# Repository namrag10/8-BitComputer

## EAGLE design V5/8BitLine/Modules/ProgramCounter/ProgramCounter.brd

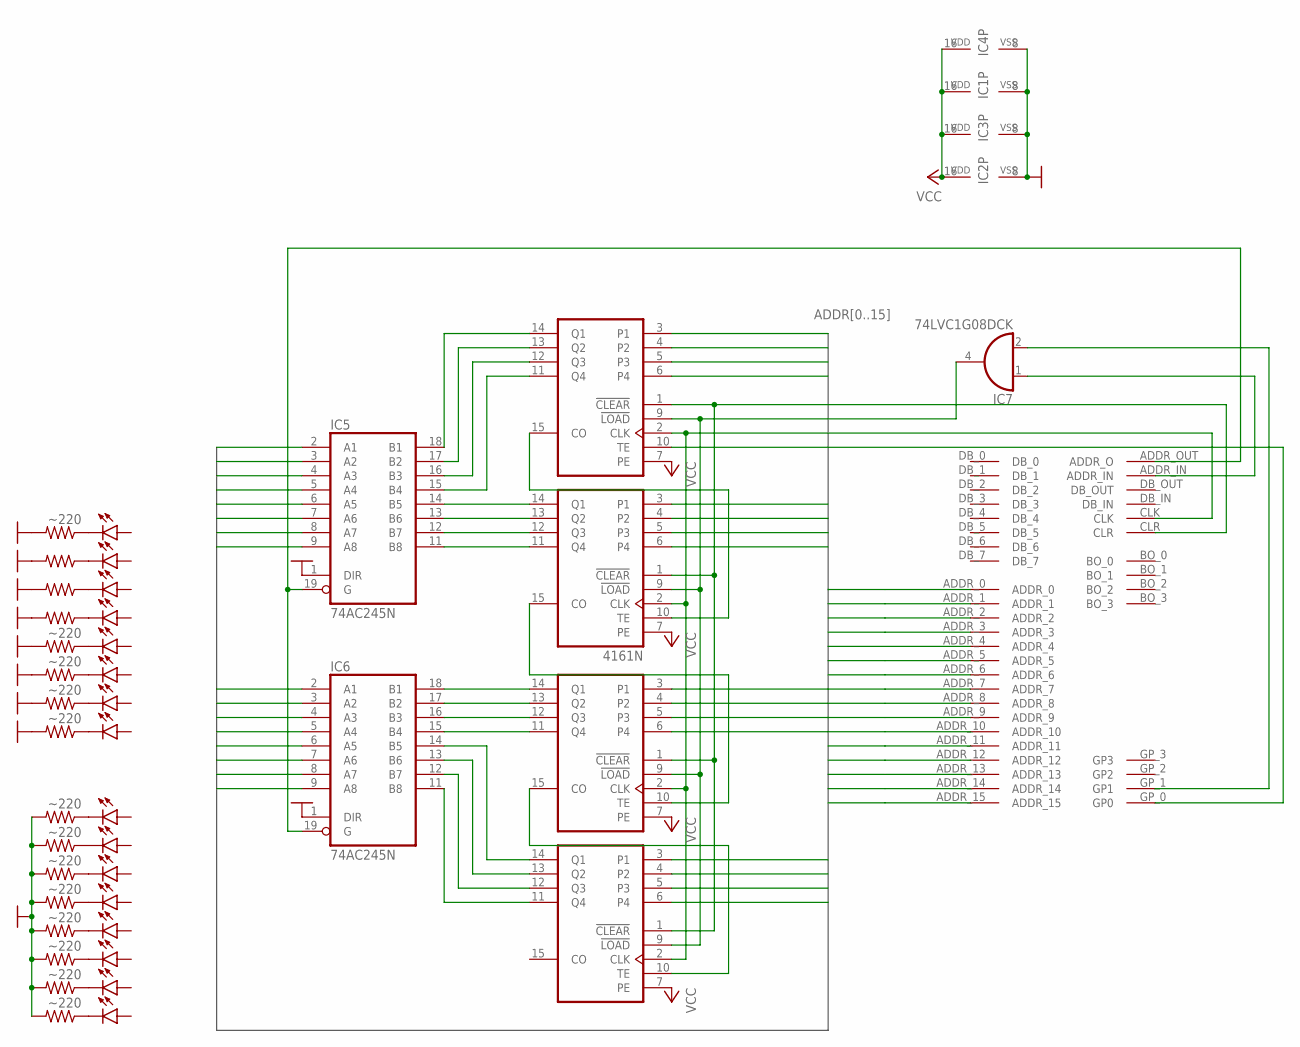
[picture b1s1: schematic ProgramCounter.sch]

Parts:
IC1, IC2, IC3, IC4: 4161N; DIL16
IC5, IC6: 74AC245N; DIL20
IC7: 74LVC1G08DCK; SC70-5
LED_A_REG_1, LED_A_REG_2, LED_A_REG_3, LED_A_REG_4, LED_A_REG_5, LED_A_REG_6, LED_A_REG_7, LED_A_REG_8, LED_A_REG_9, LED_A_REG_10, LED_A_REG_11, LED_A_REG_12, LED_A_REG_13, LED_A_REG_14, LED_A_REG_15, LED_A_REG_16: LED; LED5MM
R1, R2, R3, R4, R5, R6, R7, R8, R9, R10, R11, R12, R13, R14, R15, R16: ~220; 0204/7
U$1: BACKPLATE_INTERFACEEDGE_FINGER; BACK_INTERFACE-FOOT

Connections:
ADDR0: IC2.3 (P1), IC5.2 (A1), U$1.ADDR_0
ADDR1: IC2.4 (P2), IC5.3 (A2), U$1.ADDR_1
ADDR2: IC2.5 (P3), IC5.4 (A3), U$1.ADDR_2
ADDR3: IC2.6 (P4), IC5.5 (A4), U$1.ADDR_3
ADDR4: IC3.3 (P1), IC5.6 (A5), U$1.ADDR_4
ADDR5: IC3.4 (P2), IC5.7 (A6), U$1.ADDR_5
ADDR6: IC3.5 (P3), IC5.8 (A7), U$1.ADDR_6
ADDR7: IC3.6 (P4), IC5.9 (A8), U$1.ADDR_7
ADDR8: IC1.3 (P1), IC6.2 (A1), U$1.ADDR_8
ADDR9: IC1.4 (P2), IC6.3 (A2), U$1.ADDR_9
ADDR10: IC1.5 (P3), IC6.4 (A3), U$1.ADDR_10
ADDR11: IC1.6 (P4), IC6.5 (A4), U$1.ADDR_11
ADDR12: IC4.3 (P1), IC6.6 (A5), U$1.ADDR_12
ADDR13: IC4.4 (P2), IC6.7 (A6), U$1.ADDR_13
ADDR14: IC4.5 (P3), IC6.8 (A7), U$1.ADDR_14
ADDR15: IC4.6 (P4), IC6.9 (A8), U$1.ADDR_15
CONFIRMED_LOAD: IC1.9 (!LOAD), IC2.9 (!LOAD), IC3.9 (!LOAD), IC4.9 (!LOAD), IC7.4 (O)
GND: IC1.8 (VSS), IC2.8 (VSS), IC3.8 (VSS), IC4.8 (VSS), IC5.1 (DIR), IC5.10 (GND), IC6.1 (DIR), IC6.10 (GND), IC7.3 (GND), R1.2, R2.2, R3.2, R4.2, R5.2, R6.2, R7.2, R8.2, R9.2, R10.2, R11.2, R12.2, R13.2, R14.2, R15.2, R16.2, U$1.GND_0 (GND), U$1.GND_1 (GND)
LOAD_CONFIRMATION: IC7.2 (I1), U$1.GP_1 (GP1)
LOAD_REQUEST: IC7.1 (I0), U$1.ADDR_IN
unnamed: IC2.14 (Q1), IC5.18 (B1)
unnamed: IC2.13 (Q2), IC5.17 (B2)
unnamed: IC2.12 (Q3), IC5.16 (B3)
unnamed: IC2.11 (Q4), IC5.15 (B4)
unnamed: IC1.14 (Q1), IC6.18 (B1)
unnamed: IC3.13 (Q2), IC5.13 (B6)
unnamed: IC3.12 (Q3), IC5.12 (B7)
unnamed: IC3.11 (Q4), IC5.11 (B8)
unnamed: IC1.13 (Q2), IC6.17 (B2)
unnamed: IC1.12 (Q3), IC6.16 (B3)
unnamed: IC1.11 (Q4), IC6.15 (B4)
unnamed: IC4.11 (Q4), IC6.11 (B8)
unnamed: IC4.12 (Q3), IC6.12 (B7)
unnamed: IC4.13 (Q2), IC6.13 (B6)
unnamed: IC4.14 (Q1), IC6.14 (B5)
unnamed: IC1.2 (CLK), IC2.2 (CLK), IC3.2 (CLK), IC4.2 (CLK), U$1.CLK
unnamed: IC1.1 (!CLEAR), IC2.1 (!CLEAR), IC3.1 (!CLEAR), IC4.1 (!CLEAR), U$1.CLR
unnamed: IC2.15 (CO), IC3.10 (TE)
unnamed: IC1.10 (TE), IC3.15 (CO)
unnamed: IC1.15 (CO), IC4.10 (TE)
unnamed: IC2.10 (TE), U$1.GP_0 (GP0)
unnamed: IC5.19 (G), IC6.19 (G), U$1.ADDR_OUT (ADDR_O)
unnamed: LED_A_REG_1.K (C), R1.1
unnamed: LED_A_REG_10.K (C), R9.1
unnamed: LED_A_REG_11.K (C), R10.1
unnamed: LED_A_REG_12.K (C), R11.1
unnamed: LED_A_REG_13.K (C), R12.1
unnamed: LED_A_REG_14.K (C), R13.1
unnamed: LED_A_REG_15.K (C), R14.1
unnamed: LED_A_REG_16.K (C), R15.1
unnamed: LED_A_REG_9.K (C), R16.1
unnamed: IC3.14 (Q1), IC5.14 (B5)
unnamed: LED_A_REG_2.K (C), R2.1
unnamed: LED_A_REG_3.K (C), R3.1
unnamed: LED_A_REG_4.K (C), R4.1
unnamed: LED_A_REG_5.K (C), R5.1
unnamed: LED_A_REG_6.K (C), R6.1
unnamed: LED_A_REG_7.K (C), R7.1
unnamed: LED_A_REG_8.K (C), R8.1
VCC: IC1.7 (PE), IC1.16 (VDD), IC2.7 (PE), IC2.16 (VDD), IC3.7 (PE), IC3.16 (VDD), IC4.7 (PE), IC4.16 (VDD), IC5.20 (VCC), IC6.20 (VCC), IC7.5 (VCC), U$1.VCC_0 (VCC), U$1.VCC_1 (VCC)

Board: 2 copper layers, 40 parts (0 on the bottom side), 60 nets, no tracks yet.

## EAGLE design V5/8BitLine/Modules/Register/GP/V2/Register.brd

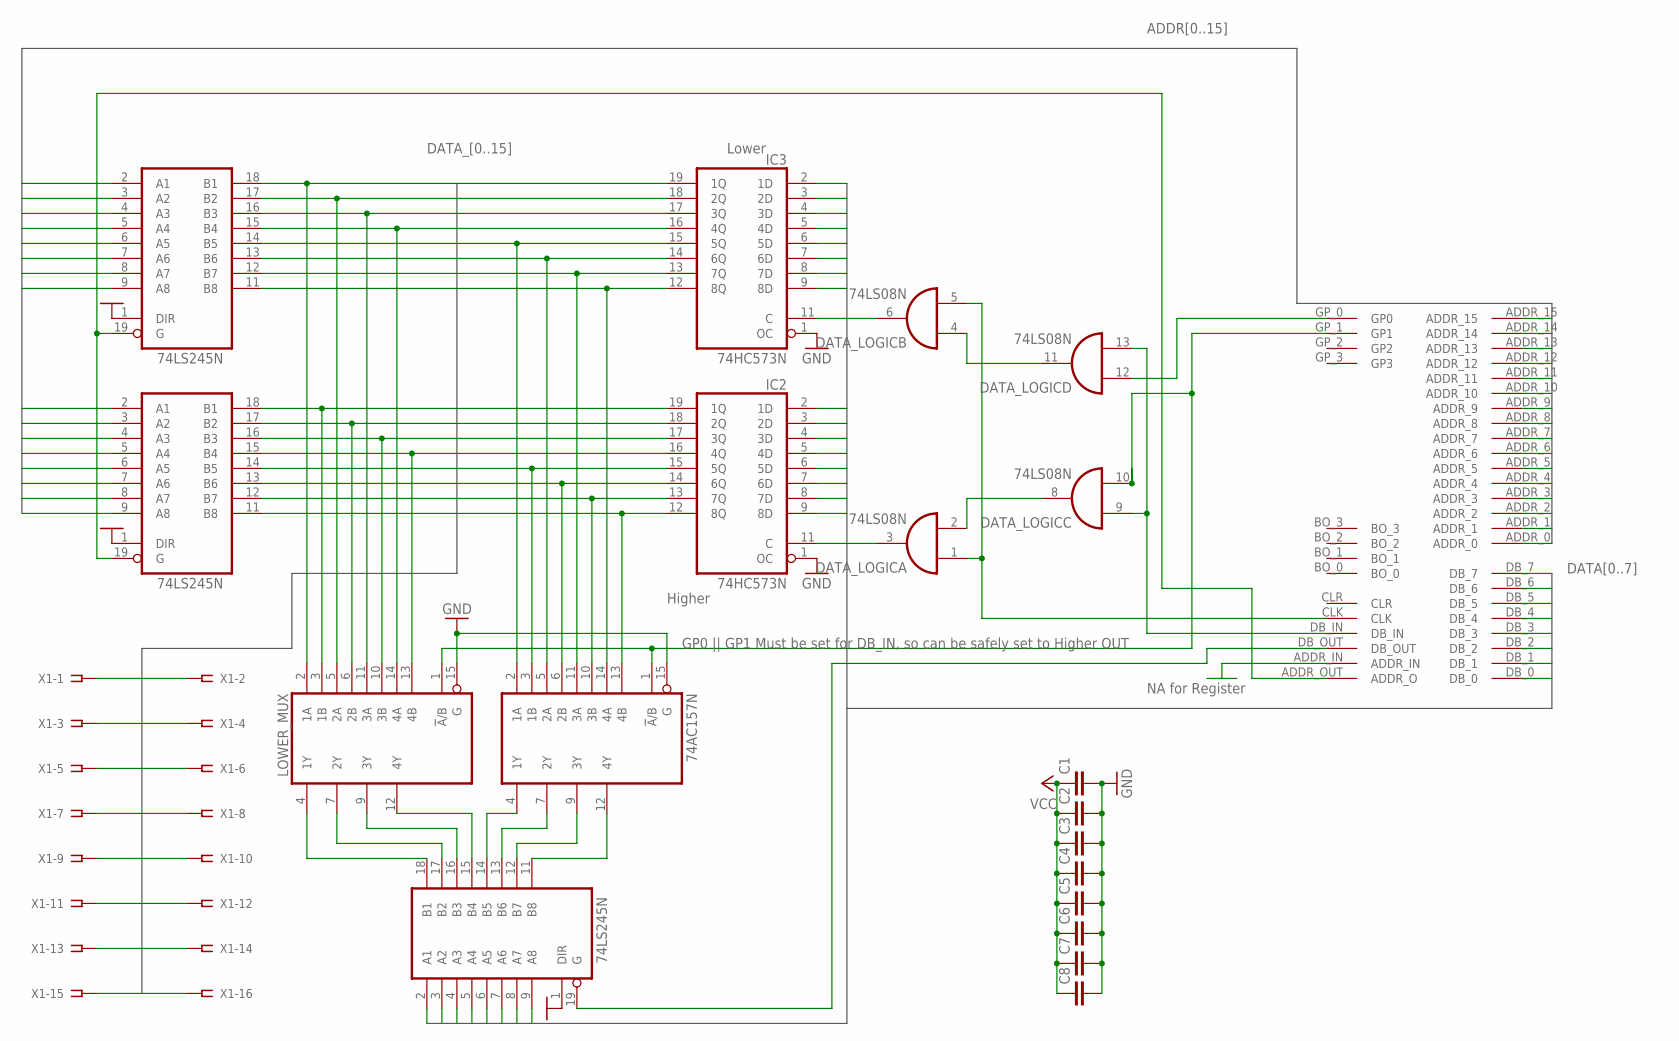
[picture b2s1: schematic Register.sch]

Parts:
ADDR_HIGHER_BUFFER: 74LS245N; DIL20
ADDR_LOWER_BUFFER: 74LS245N; DIL20
C1, C2, C3, C4, C5, C6, C7, C8: C2.5/2; C2.5-2
DATA_LOGIC: 74LS08N; DIL14
DATA_OUTPUT_BUFFER: 74LS245N; DIL20
HIGHER_MUX: 74AC157N; DIL16
IC2, IC3: 74HC573N; DIL20
LOWER_MUX: 74AC157N; DIL16
U$1: BACKPLATE_INTERFACEEDGE_FINGER; BACK_INTERFACE-FOOT
X1: SSW-108-02-G-D

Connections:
ADDR0: ADDR_LOWER_BUFFER.2 (A1), U$1.ADDR_0
ADDR1: ADDR_LOWER_BUFFER.3 (A2), U$1.ADDR_1
ADDR2: ADDR_LOWER_BUFFER.4 (A3), U$1.ADDR_2
ADDR3: ADDR_LOWER_BUFFER.5 (A4), U$1.ADDR_3
ADDR4: ADDR_LOWER_BUFFER.6 (A5), U$1.ADDR_4
ADDR5: ADDR_LOWER_BUFFER.7 (A6), U$1.ADDR_5
ADDR6: ADDR_LOWER_BUFFER.8 (A7), U$1.ADDR_6
ADDR7: ADDR_LOWER_BUFFER.9 (A8), U$1.ADDR_7
ADDR8: ADDR_HIGHER_BUFFER.2 (A1), U$1.ADDR_8
ADDR9: ADDR_HIGHER_BUFFER.3 (A2), U$1.ADDR_9
ADDR10: ADDR_HIGHER_BUFFER.4 (A3), U$1.ADDR_10
ADDR11: ADDR_HIGHER_BUFFER.5 (A4), U$1.ADDR_11
ADDR12: ADDR_HIGHER_BUFFER.6 (A5), U$1.ADDR_12
ADDR13: ADDR_HIGHER_BUFFER.7 (A6), U$1.ADDR_13
ADDR14: ADDR_HIGHER_BUFFER.8 (A7), U$1.ADDR_14
ADDR15: ADDR_HIGHER_BUFFER.9 (A8), U$1.ADDR_15
CLK: DATA_LOGIC.1 (I0), DATA_LOGIC.5 (I1), U$1.CLK
CTRL_ADDR_OUT: ADDR_HIGHER_BUFFER.19 (G), ADDR_LOWER_BUFFER.19 (G), U$1.ADDR_OUT (ADDR_O)
CTRL_DB_IN: DATA_LOGIC.9 (I0), DATA_LOGIC.13 (I1), U$1.DB_IN
CTRL_DB_OUT: DATA_OUTPUT_BUFFER.19 (G), U$1.DB_OUT
DATA0: DATA_OUTPUT_BUFFER.2 (A1), IC2.2 (1D), IC3.2 (1D), U$1.DB_0
DATA1: DATA_OUTPUT_BUFFER.3 (A2), IC2.3 (2D), IC3.3 (2D), U$1.DB_1
DATA2: DATA_OUTPUT_BUFFER.4 (A3), IC2.4 (3D), IC3.4 (3D), U$1.DB_2
DATA3: DATA_OUTPUT_BUFFER.5 (A4), IC2.5 (4D), IC3.5 (4D), U$1.DB_3
DATA4: DATA_OUTPUT_BUFFER.6 (A5), IC2.6 (5D), IC3.6 (5D), U$1.DB_4
DATA5: DATA_OUTPUT_BUFFER.7 (A6), IC2.7 (6D), IC3.7 (6D), U$1.DB_5
DATA6: DATA_OUTPUT_BUFFER.8 (A7), IC2.8 (7D), IC3.8 (7D), U$1.DB_6
DATA7: DATA_OUTPUT_BUFFER.9 (A8), IC2.9 (8D), IC3.9 (8D), U$1.DB_7
DATA_0: ADDR_LOWER_BUFFER.18 (B1), IC3.19 (1Q), LOWER_MUX.2 (1A), X1.15
DATA_1: ADDR_LOWER_BUFFER.17 (B2), IC3.18 (2Q), LOWER_MUX.5 (2A), X1.13
DATA_2: ADDR_LOWER_BUFFER.16 (B3), IC3.17 (3Q), LOWER_MUX.11 (3A), X1.11
DATA_3: ADDR_LOWER_BUFFER.15 (B4), IC3.16 (4Q), LOWER_MUX.14 (4A), X1.9
DATA_4: ADDR_LOWER_BUFFER.14 (B5), HIGHER_MUX.2 (1A), IC3.15 (5Q), X1.7
DATA_5: ADDR_LOWER_BUFFER.13 (B6), HIGHER_MUX.5 (2A), IC3.14 (6Q), X1.5
DATA_6: ADDR_LOWER_BUFFER.12 (B7), HIGHER_MUX.11 (3A), IC3.13 (7Q), X1.3
DATA_7: ADDR_LOWER_BUFFER.11 (B8), HIGHER_MUX.14 (4A), IC3.12 (8Q), X1.1
DATA_8: ADDR_HIGHER_BUFFER.18 (B1), IC2.19 (1Q), LOWER_MUX.3 (1B), X1.2
DATA_9: ADDR_HIGHER_BUFFER.17 (B2), IC2.18 (2Q), LOWER_MUX.6 (2B), X1.4
DATA_10: ADDR_HIGHER_BUFFER.16 (B3), IC2.17 (3Q), LOWER_MUX.10 (3B), X1.6
DATA_11: ADDR_HIGHER_BUFFER.15 (B4), IC2.16 (4Q), LOWER_MUX.13 (4B), X1.8
DATA_12: ADDR_HIGHER_BUFFER.14 (B5), HIGHER_MUX.3 (1B), IC2.15 (5Q), X1.10
DATA_13: ADDR_HIGHER_BUFFER.13 (B6), HIGHER_MUX.6 (2B), IC2.14 (6Q), X1.12
DATA_14: ADDR_HIGHER_BUFFER.12 (B7), HIGHER_MUX.10 (3B), IC2.13 (7Q), X1.14
DATA_15: ADDR_HIGHER_BUFFER.11 (B8), HIGHER_MUX.13 (4B), IC2.12 (8Q), X1.16
GND: ADDR_HIGHER_BUFFER.1 (DIR), ADDR_HIGHER_BUFFER.10 (GND), ADDR_LOWER_BUFFER.1 (DIR), ADDR_LOWER_BUFFER.10 (GND), C1.2, C2.2, C3.2, C4.2, C5.2, C6.2, C7.2, C8.2, DATA_LOGIC.7 (GND), DATA_OUTPUT_BUFFER.1 (DIR), DATA_OUTPUT_BUFFER.10 (GND), HIGHER_MUX.8 (GND), HIGHER_MUX.15 (G), IC2.1 (OC), IC2.10 (GND), IC3.1 (OC), IC3.10 (GND), LOWER_MUX.8 (GND), LOWER_MUX.15 (G), U$1.GND_0 (GND), U$1.GND_1 (GND)
GP_0: DATA_LOGIC.12 (I0), U$1.GP_0 (GP0)
GP_1: DATA_LOGIC.10 (I1), HIGHER_MUX.1 (!A!/B), LOWER_MUX.1 (!A!/B), U$1.GP_1 (GP1)
unnamed: DATA_OUTPUT_BUFFER.18 (B1), LOWER_MUX.4 (1Y)
unnamed: DATA_OUTPUT_BUFFER.17 (B2), LOWER_MUX.7 (2Y)
unnamed: DATA_LOGIC.6 (O), IC3.11 (C)
unnamed: DATA_LOGIC.3 (O), IC2.11 (C)
unnamed: DATA_LOGIC.4 (I0), DATA_LOGIC.11 (O)
unnamed: DATA_LOGIC.2 (I1), DATA_LOGIC.8 (O)
unnamed: DATA_OUTPUT_BUFFER.16 (B3), LOWER_MUX.9 (3Y)
unnamed: DATA_OUTPUT_BUFFER.15 (B4), LOWER_MUX.12 (4Y)
unnamed: DATA_OUTPUT_BUFFER.14 (B5), HIGHER_MUX.4 (1Y)
unnamed: DATA_OUTPUT_BUFFER.13 (B6), HIGHER_MUX.7 (2Y)
unnamed: DATA_OUTPUT_BUFFER.12 (B7), HIGHER_MUX.9 (3Y)
unnamed: DATA_OUTPUT_BUFFER.11 (B8), HIGHER_MUX.12 (4Y)
VCC: ADDR_HIGHER_BUFFER.20 (VCC), ADDR_LOWER_BUFFER.20 (VCC), C1.1, C2.1, C3.1, C4.1, C5.1, C6.1, C7.1, C8.1, DATA_LOGIC.14 (VCC), DATA_OUTPUT_BUFFER.20 (VCC), HIGHER_MUX.16 (VCC), IC2.20 (VCC), IC3.20 (VCC), LOWER_MUX.16 (VCC), U$1.VCC_0 (VCC), U$1.VCC_1 (VCC)

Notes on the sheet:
Lower
Higher
GP0 || GP1 Must be set for DB_IN, so can be safely set to Higher OUT
NA for Register

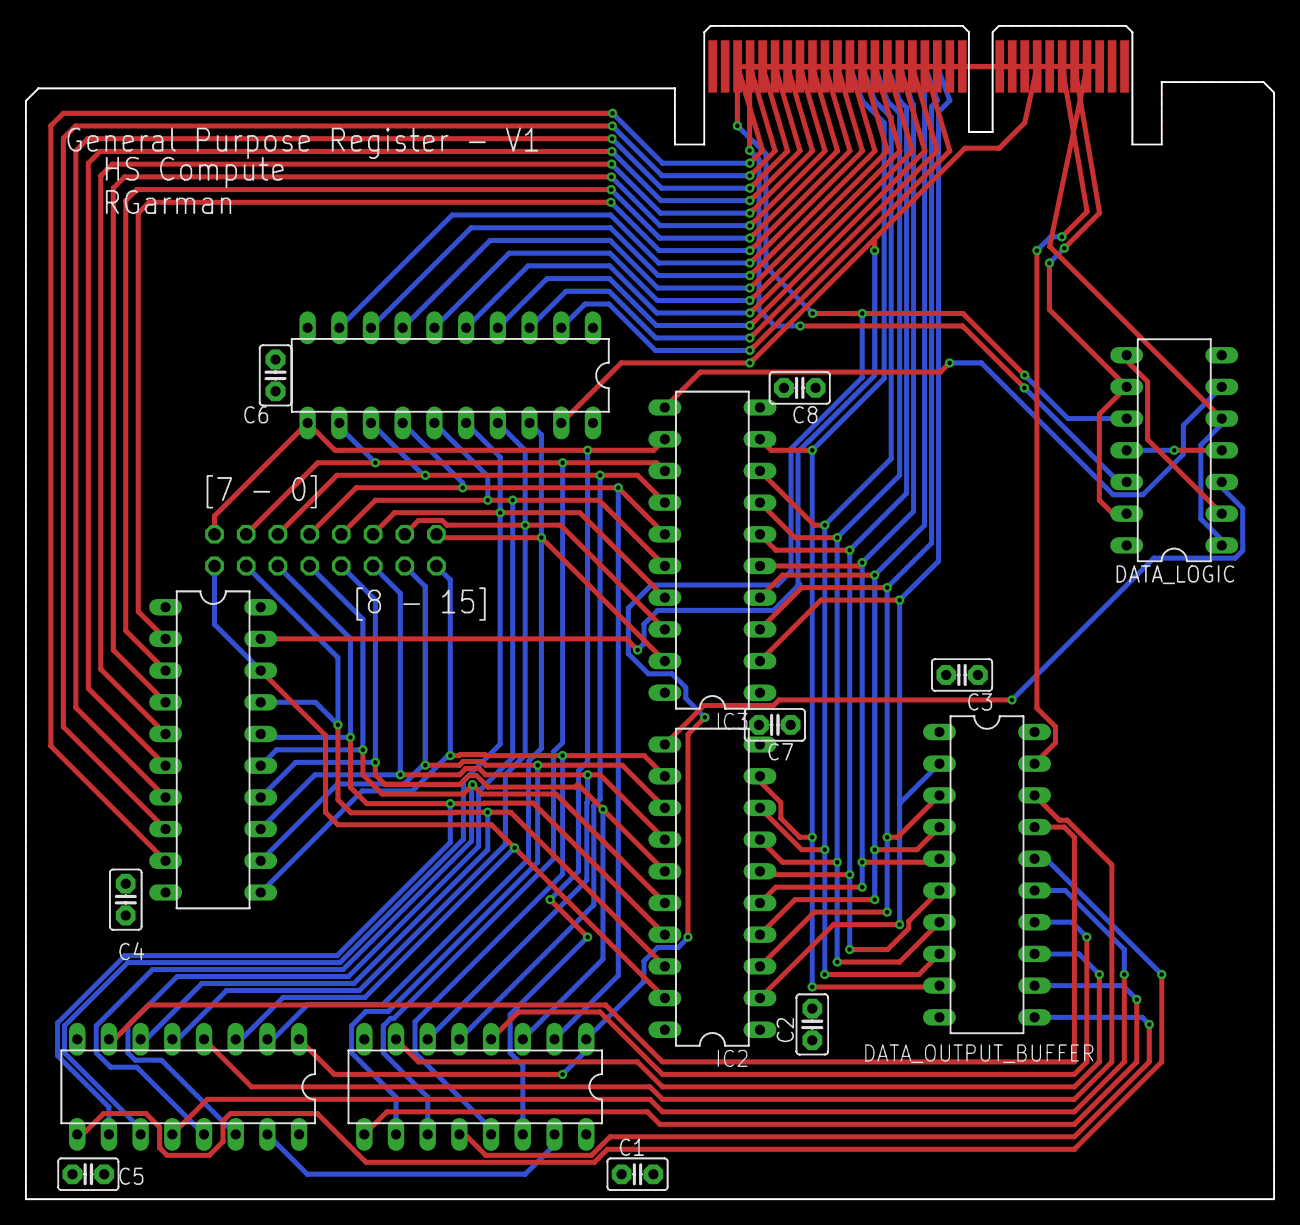
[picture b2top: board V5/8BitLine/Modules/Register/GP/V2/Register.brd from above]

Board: 2 copper layers, 100.0 x 94.0 mm, 18 parts (1 on the bottom side), 60 nets.

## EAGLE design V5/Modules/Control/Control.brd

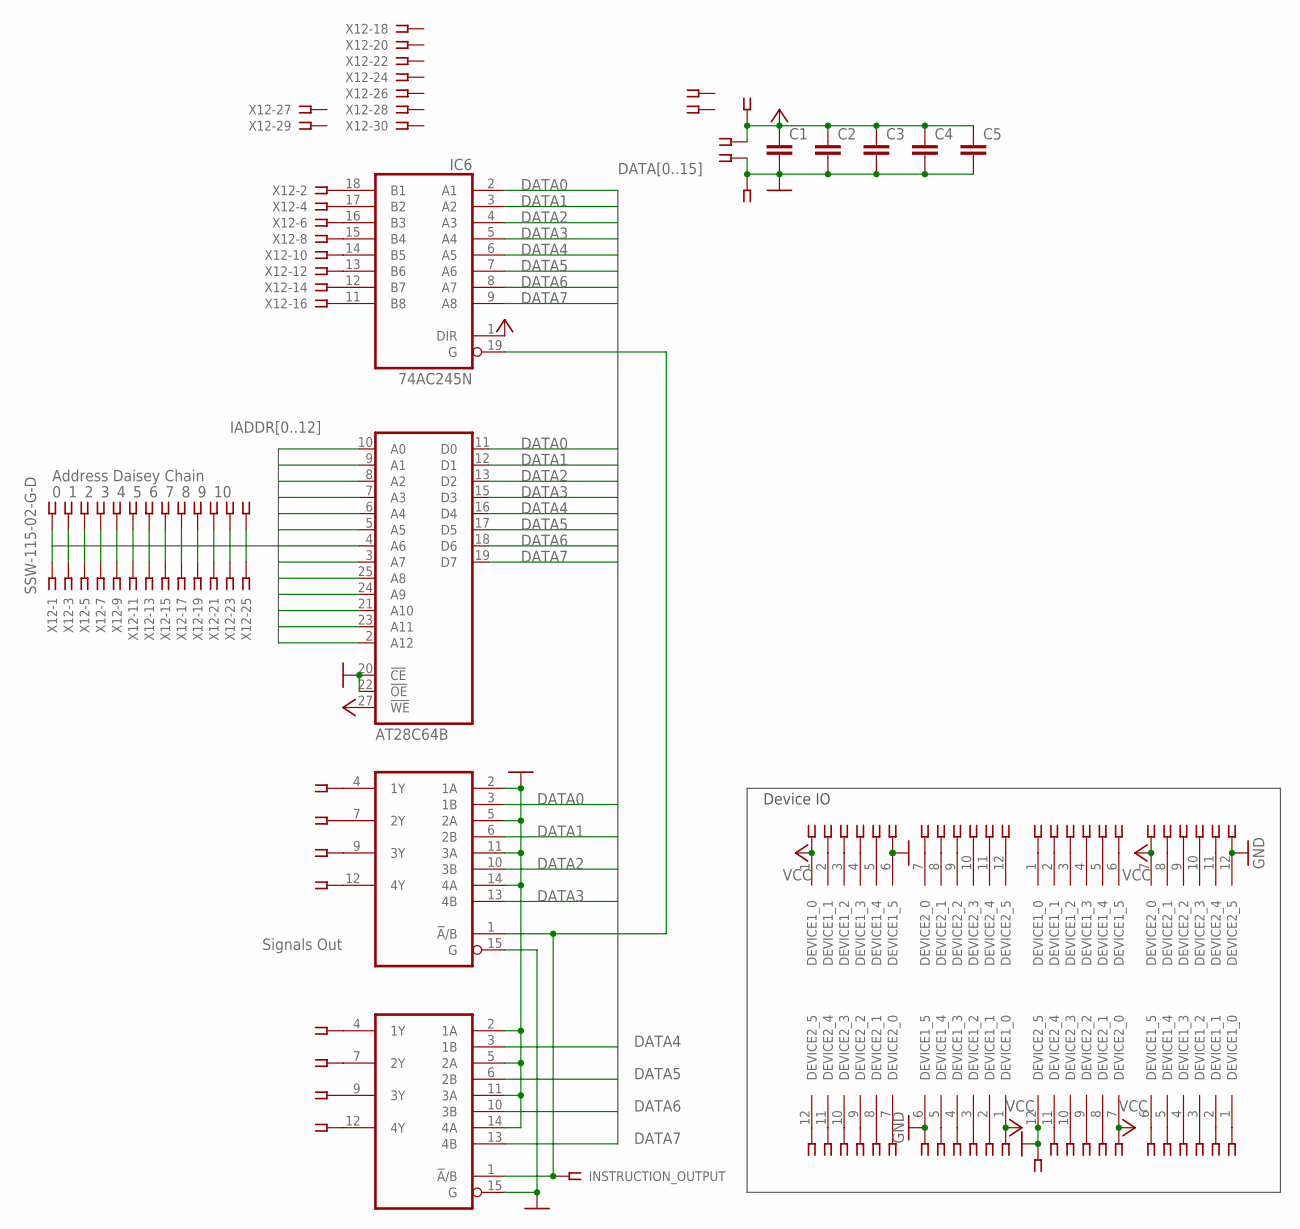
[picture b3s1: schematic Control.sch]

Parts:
C1, C2, C3, C4, C5: C2.5/2; C2.5-2
IC4, IC5: 74AC157N; DIL16
IC6: 74AC245N; DIL20
INSTRUCTION_OUTPUT: SSW-101-02-G-S
U$1, U$2, U$4, U$5: CONTROL_SIG-INT; CONTROL_SIG-INT-FOOT
U$3: AT28C64B; DIP28-WIDE
X1, X2, X3, X4, X6, X7, X8, X9: SSW-106-02-G-S
X5: SSW-108-02-G-S
X10: SSW-113-02-G-S
X11: SSW-102-02-G-S
X12: SSW-115-02-G-D
X13: SSW-104-02-G-S

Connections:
DATA0: IC4.3 (1B), IC6.2 (A1), U$3.11 (D0)
DATA1: IC4.6 (2B), IC6.3 (A2), U$3.12 (D1)
DATA2: IC4.10 (3B), IC6.4 (A3), U$3.13 (D2)
DATA3: IC4.13 (4B), IC6.5 (A4), U$3.15 (D3)
DATA4: IC5.3 (1B), IC6.6 (A5), U$3.16 (D4)
DATA5: IC5.6 (2B), IC6.7 (A6), U$3.17 (D5)
DATA6: IC5.10 (3B), IC6.8 (A7), U$3.18 (D6)
DATA7: IC5.13 (4B), IC6.9 (A8), U$3.19 (D7)
GND: C1.2, C2.2, C3.2, C4.2, C5.2, IC4.2 (1A), IC4.5 (2A), IC4.8 (GND), IC4.11 (3A), IC4.14 (4A), IC4.15 (G), IC5.2 (1A), IC5.5 (2A), IC5.8 (GND), IC5.11 (3A), IC5.14 (4A), IC5.15 (G), IC6.10 (GND), U$1.6 (DEVICE1_5), U$2.12 (DEVICE2_5), U$3.14 (GND), U$3.20 (!CE), U$3.22 (!OE), U$4.12 (DEVICE2_5), U$5.6 (DEVICE1_5), X1.1, X4.1, X7.1, X8.1, X11.2, X13.4
IADDR0: U$3.10 (A0), X10.13, X12.1
IADDR1: U$3.9 (A1), X10.12, X12.3
IADDR2: U$3.8 (A2), X10.11, X12.5
IADDR3: U$3.7 (A3), X10.10, X12.7
IADDR4: U$3.6 (A4), X10.9, X12.9
IADDR5: U$3.5 (A5), X10.8, X12.11
IADDR6: U$3.4 (A6), X10.7, X12.13
IADDR7: U$3.3 (A7), X10.6, X12.15
IADDR8: U$3.25 (A8), X10.5, X12.17
IADDR9: U$3.24 (A9), X10.4, X12.19
IADDR10: U$3.21 (A10), X10.3, X12.21
IADDR11: U$3.23 (A11), X10.2, X12.23
IADDR12: U$3.2 (A12), X10.1, X12.25
unnamed: U$2.6 (DEVICE1_5), X6.1
unnamed: U$2.5 (DEVICE1_4), X6.2
unnamed: U$2.4 (DEVICE1_3), X6.3
unnamed: U$2.3 (DEVICE1_2), X6.4
unnamed: U$2.2 (DEVICE1_1), X6.5
unnamed: U$2.1 (DEVICE1_0), X6.6
unnamed: U$2.11 (DEVICE2_4), X7.2
unnamed: U$2.10 (DEVICE2_3), X7.3
unnamed: U$2.9 (DEVICE2_2), X7.4
unnamed: U$2.8 (DEVICE2_1), X7.5
unnamed: U$4.6 (DEVICE1_5), X3.1
unnamed: U$4.5 (DEVICE1_4), X3.2
unnamed: U$4.4 (DEVICE1_3), X3.3
unnamed: U$4.3 (DEVICE1_2), X3.4
unnamed: U$4.2 (DEVICE1_1), X3.5
unnamed: U$4.1 (DEVICE1_0), X3.6
unnamed: U$4.11 (DEVICE2_4), X4.2
unnamed: U$4.10 (DEVICE2_3), X4.3
unnamed: U$4.9 (DEVICE2_2), X4.4
unnamed: U$4.8 (DEVICE2_1), X4.5
unnamed: U$5.5 (DEVICE1_4), X1.2
unnamed: U$5.4 (DEVICE1_3), X1.3
unnamed: U$5.3 (DEVICE1_2), X1.4
unnamed: U$5.2 (DEVICE1_1), X1.5
unnamed: U$5.12 (DEVICE2_5), X2.1
unnamed: U$5.11 (DEVICE2_4), X2.2
unnamed: U$5.10 (DEVICE2_3), X2.3
unnamed: U$5.9 (DEVICE2_2), X2.4
unnamed: U$5.8 (DEVICE2_1), X2.5
unnamed: U$5.7 (DEVICE2_0), X2.6
unnamed: U$1.5 (DEVICE1_4), X8.2
unnamed: U$1.4 (DEVICE1_3), X8.3
unnamed: U$1.3 (DEVICE1_2), X8.4
unnamed: U$1.2 (DEVICE1_1), X8.5
unnamed: U$1.12 (DEVICE2_5), X9.1
unnamed: U$1.11 (DEVICE2_4), X9.2
unnamed: U$1.10 (DEVICE2_3), X9.3
unnamed: U$1.9 (DEVICE2_2), X9.4
unnamed: U$1.8 (DEVICE2_1), X9.5
unnamed: U$1.7 (DEVICE2_0), X9.6
unnamed: IC6.18 (B1), X12.2
unnamed: IC6.17 (B2), X12.4
unnamed: IC6.16 (B3), X12.6
unnamed: IC6.15 (B4), X12.8
unnamed: IC6.14 (B5), X12.10
unnamed: IC6.13 (B6), X12.12
unnamed: IC6.12 (B7), X12.14
unnamed: IC6.11 (B8), X12.16
unnamed: IC5.12 (4Y), X5.1
unnamed: IC5.9 (3Y), X5.2
unnamed: IC4.1 (!A!/B), IC5.1 (!A!/B), IC6.19 (G), INSTRUCTION_OUTPUT.1
unnamed: IC5.7 (2Y), X5.3
unnamed: IC5.4 (1Y), X5.4
unnamed: IC4.12 (4Y), X5.5
unnamed: IC4.9 (3Y), X5.6
unnamed: IC4.7 (2Y), X5.7
unnamed: IC4.4 (1Y), X5.8
VCC: C1.1, C2.1, C3.1, C4.1, C5.1, IC4.16 (VCC), IC5.16 (VCC), IC6.1 (DIR), IC6.20 (VCC), U$1.1 (DEVICE1_0), U$2.7 (DEVICE2_0), U$3.27 (!WE), U$3.28 (VCC), U$4.7 (DEVICE2_0), U$5.1 (DEVICE1_0), X1.6, X4.6, X7.6, X8.6, X11.1, X13.1

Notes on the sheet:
Device IO
Address Daisey Chain
Signals Out

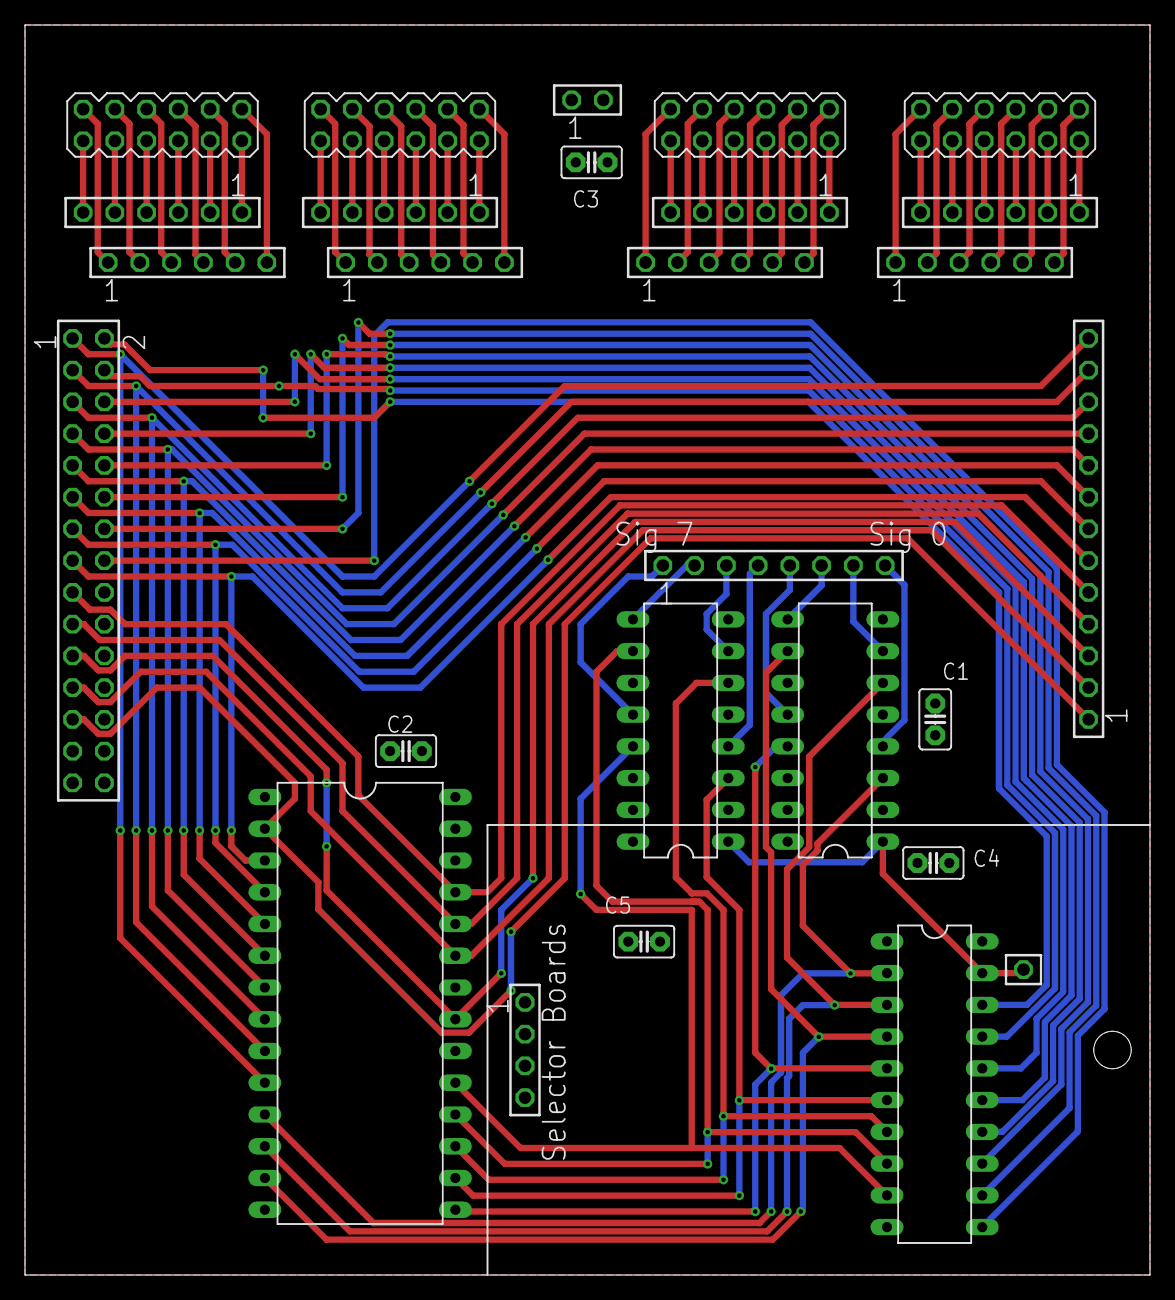
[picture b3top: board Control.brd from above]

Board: 2 copper layers, 90.0 x 100.0 mm, 27 parts (0 on the bottom side), 80 nets.

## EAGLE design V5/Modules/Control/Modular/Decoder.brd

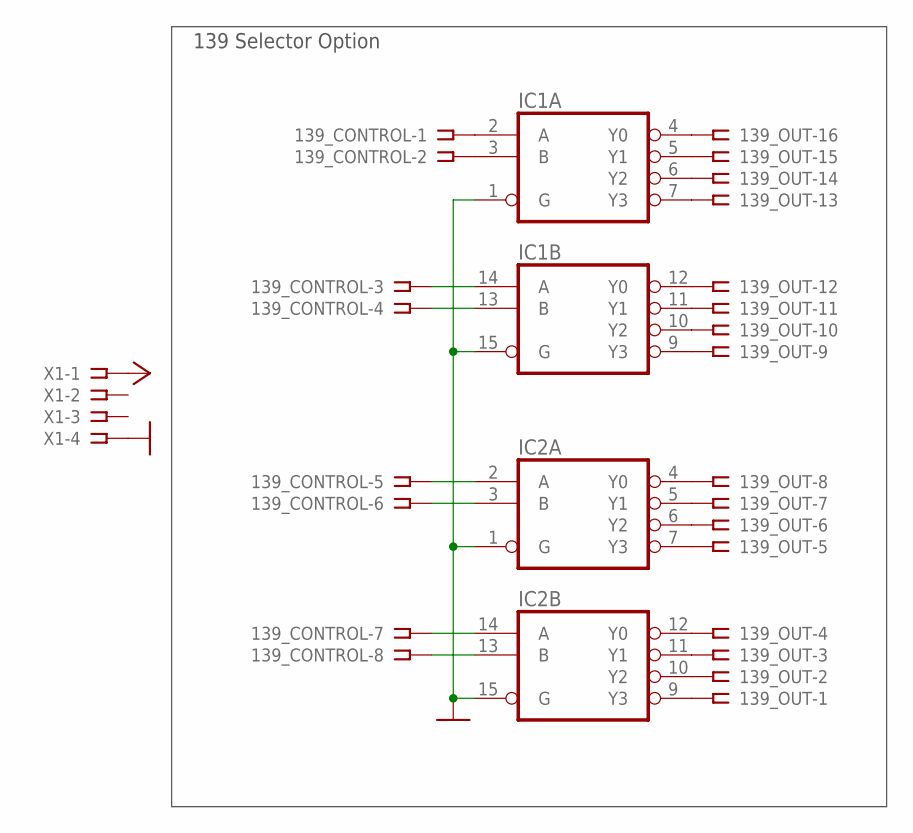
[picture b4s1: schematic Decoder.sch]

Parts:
139_CONTROL: SSW-108-02-G-S
139_OUT: SSW-116-02-G-S
IC1, IC2: 74AC139N; DIL16
X1: SSW-104-02-G-S

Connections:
GND: IC1.1 (G), IC1.8 (GND), IC1.15 (G), IC2.1 (G), IC2.8 (GND), IC2.15 (G), X1.4
unnamed: 139_OUT.13, IC1.7 (Y3)
unnamed: 139_OUT.14, IC1.6 (Y2)
unnamed: 139_OUT.15, IC1.5 (Y1)
unnamed: 139_OUT.16, IC1.4 (Y0)
unnamed: 139_OUT.9, IC1.9 (Y3)
unnamed: 139_OUT.10, IC1.10 (Y2)
unnamed: 139_OUT.11, IC1.11 (Y1)
unnamed: 139_OUT.12, IC1.12 (Y0)
unnamed: 139_OUT.5, IC2.7 (Y3)
unnamed: 139_OUT.6, IC2.6 (Y2)
unnamed: 139_OUT.7, IC2.5 (Y1)
unnamed: 139_OUT.8, IC2.4 (Y0)
unnamed: 139_OUT.1, IC2.9 (Y3)
unnamed: 139_OUT.2, IC2.10 (Y2)
unnamed: 139_OUT.3, IC2.11 (Y1)
unnamed: 139_OUT.4, IC2.12 (Y0)
unnamed: 139_CONTROL.1, IC1.2 (A)
unnamed: 139_CONTROL.2, IC1.3 (B)
unnamed: 139_CONTROL.8, IC2.13 (B)
unnamed: 139_CONTROL.7, IC2.14 (A)
unnamed: 139_CONTROL.6, IC2.3 (B)
unnamed: 139_CONTROL.5, IC2.2 (A)
unnamed: 139_CONTROL.4, IC1.13 (B)
unnamed: 139_CONTROL.3, IC1.14 (A)
VCC: IC1.16 (VCC), IC2.16 (VCC), X1.1

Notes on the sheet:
139 Selector Option

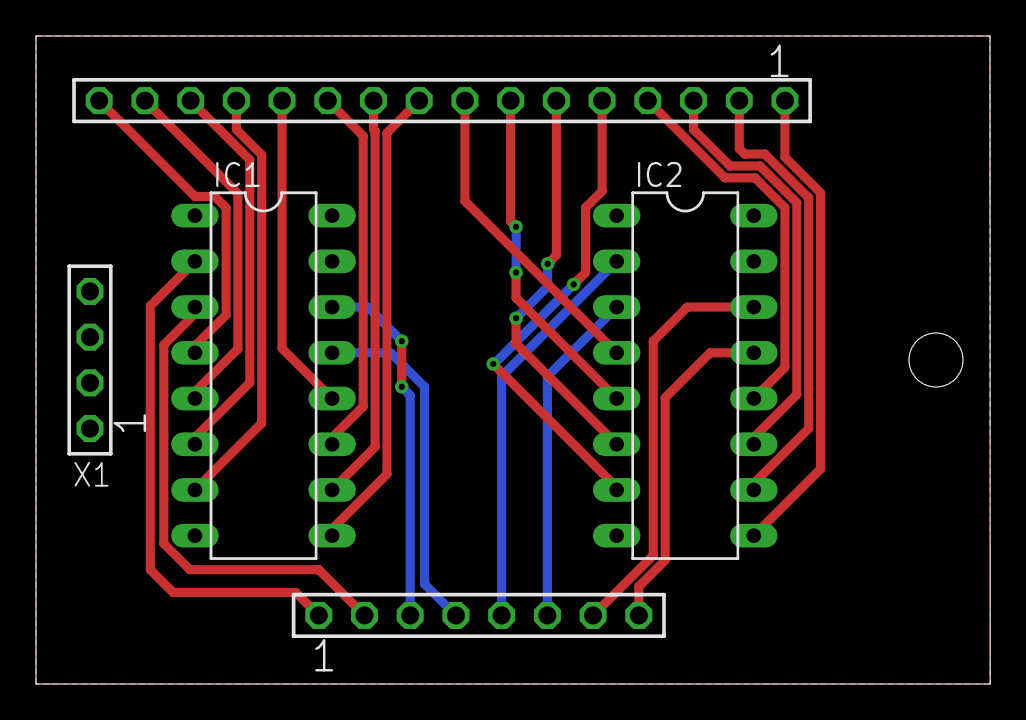
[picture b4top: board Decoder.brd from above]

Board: 2 copper layers, 53.0 x 36.0 mm, 5 parts (0 on the bottom side), 26 nets.

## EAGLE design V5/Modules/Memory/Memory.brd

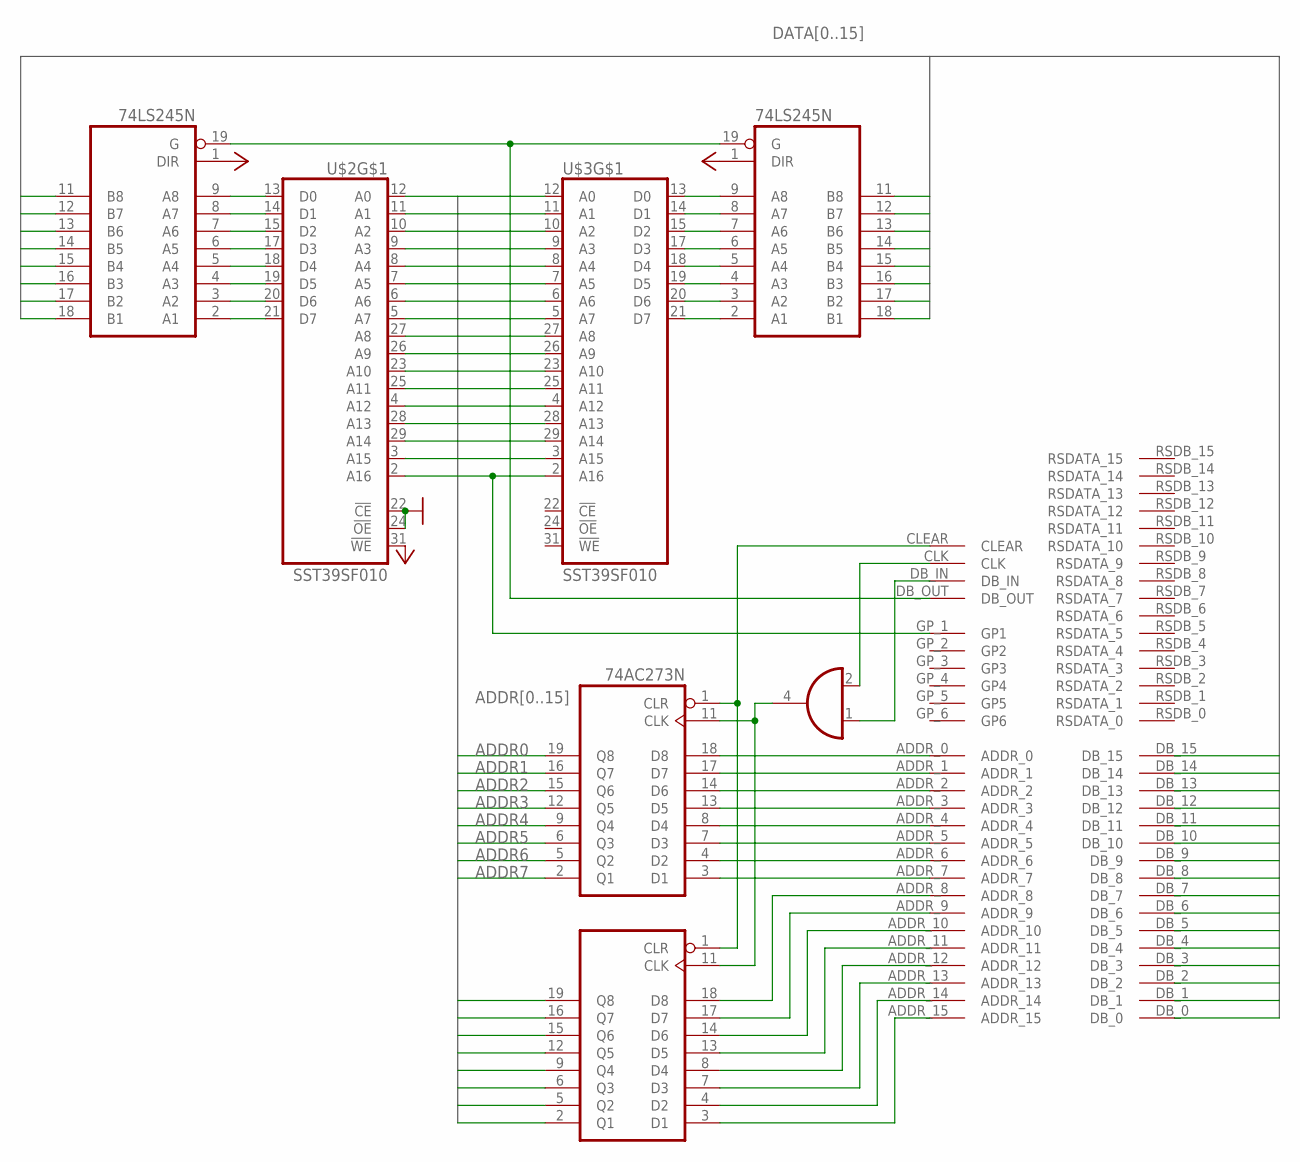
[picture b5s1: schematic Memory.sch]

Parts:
IC1, IC2: 74AC273N; DIL20
IC4: 74AHC1G08DCK; SC70-5
OUTPUT_BUFFER_MEMORY, OUTPUT_BUFFER_MEMORY1: 74LS245N; DIL20
U$1: BACKPLATE_INTERFACE; BACK_INTERFACE-FOOT
U$2, U$3: SST39SF010; DIP32-WIDE

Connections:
ADDR0: IC1.19 (Q8), U$2.12 (A0), U$3.12 (A0)
ADDR1: IC1.16 (Q7), U$2.11 (A1), U$3.11 (A1)
ADDR2: IC1.15 (Q6), U$2.10 (A2), U$3.10 (A2)
ADDR3: IC1.12 (Q5), U$2.9 (A3), U$3.9 (A3)
ADDR4: IC1.9 (Q4), U$2.8 (A4), U$3.8 (A4)
ADDR5: IC1.6 (Q3), U$2.7 (A5), U$3.7 (A5)
ADDR6: IC1.5 (Q2), U$2.6 (A6), U$3.6 (A6)
ADDR7: IC1.2 (Q1), U$2.5 (A7), U$3.5 (A7)
ADDR8: IC2.19 (Q8), U$2.27 (A8), U$3.27 (A8)
ADDR9: IC2.16 (Q7), U$2.26 (A9), U$3.26 (A9)
ADDR10: IC2.15 (Q6), U$2.23 (A10), U$3.23 (A10)
ADDR11: IC2.12 (Q5), U$2.25 (A11), U$3.25 (A11)
ADDR12: IC2.9 (Q4), U$2.4 (A12), U$3.4 (A12)
ADDR13: IC2.6 (Q3), U$2.28 (A13), U$3.28 (A13)
ADDR14: IC2.5 (Q2), U$2.3 (A15), U$2.29 (A14), U$3.29 (A14)
ADDR15: IC2.2 (Q1), U$3.3 (A15)
DATA0: OUTPUT_BUFFER_MEMORY.11 (B8), U$1.DB_0
DATA1: OUTPUT_BUFFER_MEMORY.12 (B7), U$1.DB_1
DATA2: OUTPUT_BUFFER_MEMORY.13 (B6), U$1.DB_2
DATA3: OUTPUT_BUFFER_MEMORY.14 (B5), U$1.DB_3
DATA4: OUTPUT_BUFFER_MEMORY.15 (B4), U$1.DB_4
DATA5: OUTPUT_BUFFER_MEMORY.16 (B3), U$1.DB_5
DATA6: OUTPUT_BUFFER_MEMORY.17 (B2), U$1.DB_6
DATA7: OUTPUT_BUFFER_MEMORY.18 (B1), U$1.DB_7
DATA8: OUTPUT_BUFFER_MEMORY1.11 (B8), U$1.DB_8
DATA9: OUTPUT_BUFFER_MEMORY1.12 (B7), U$1.DB_9
DATA10: OUTPUT_BUFFER_MEMORY1.13 (B6), U$1.DB_10
DATA11: OUTPUT_BUFFER_MEMORY1.14 (B5), U$1.DB_11
DATA12: OUTPUT_BUFFER_MEMORY1.15 (B4), U$1.DB_12
DATA13: OUTPUT_BUFFER_MEMORY1.16 (B3), U$1.DB_13
DATA14: OUTPUT_BUFFER_MEMORY1.17 (B2), U$1.DB_14
DATA15: OUTPUT_BUFFER_MEMORY1.18 (B1), U$1.DB_15
GND: IC1.10 (GND), IC2.10 (GND), IC4.3 (GND), OUTPUT_BUFFER_MEMORY.10 (GND), OUTPUT_BUFFER_MEMORY1.10 (GND), U$1.GND, U$1.GND2 (GND), U$2.16 (GND), U$2.22 (!CE), U$2.24 (!OE), U$3.16 (GND)
unnamed: IC1.18 (D8), U$1.ADDR_0
unnamed: IC1.17 (D7), U$1.ADDR_1
unnamed: IC1.14 (D6), U$1.ADDR_2
unnamed: IC1.13 (D5), U$1.ADDR_3
unnamed: IC1.8 (D4), U$1.ADDR_4
unnamed: IC1.7 (D3), U$1.ADDR_5
unnamed: IC1.4 (D2), U$1.ADDR_6
unnamed: IC1.3 (D1), U$1.ADDR_7
unnamed: IC2.18 (D8), U$1.ADDR_8
unnamed: IC2.17 (D7), U$1.ADDR_9
unnamed: IC2.14 (D6), U$1.ADDR_10
unnamed: IC2.13 (D5), U$1.ADDR_11
unnamed: IC2.8 (D4), U$1.ADDR_12
unnamed: IC2.7 (D3), U$1.ADDR_13
unnamed: IC2.4 (D2), U$1.ADDR_14
unnamed: IC2.3 (D1), U$1.ADDR_15
unnamed: U$1.GP_1 (GP1), U$2.2 (A16), U$3.2 (A16)
unnamed: IC1.1 (CLR), IC2.1 (CLR), U$1.CLEAR
unnamed: IC1.11 (CLK), IC2.11 (CLK), IC4.4 (O)
unnamed: OUTPUT_BUFFER_MEMORY.19 (G), OUTPUT_BUFFER_MEMORY1.19 (G), U$1.DB_OUT
unnamed: IC4.1 (I0), U$1.DB_IN
unnamed: IC4.2 (I1), U$1.CLK
unnamed: OUTPUT_BUFFER_MEMORY.2 (A1), U$2.21 (D7)
unnamed: OUTPUT_BUFFER_MEMORY.3 (A2), U$2.20 (D6)
unnamed: OUTPUT_BUFFER_MEMORY.4 (A3), U$2.19 (D5)
unnamed: OUTPUT_BUFFER_MEMORY.5 (A4), U$2.18 (D4)
unnamed: OUTPUT_BUFFER_MEMORY.6 (A5), U$2.17 (D3)
unnamed: OUTPUT_BUFFER_MEMORY.7 (A6), U$2.15 (D2)
unnamed: OUTPUT_BUFFER_MEMORY.8 (A7), U$2.14 (D1)
unnamed: OUTPUT_BUFFER_MEMORY.9 (A8), U$2.13 (D0)
unnamed: OUTPUT_BUFFER_MEMORY1.2 (A1), U$3.21 (D7)
unnamed: OUTPUT_BUFFER_MEMORY1.3 (A2), U$3.20 (D6)
unnamed: OUTPUT_BUFFER_MEMORY1.4 (A3), U$3.19 (D5)
unnamed: OUTPUT_BUFFER_MEMORY1.5 (A4), U$3.18 (D4)
unnamed: OUTPUT_BUFFER_MEMORY1.6 (A5), U$3.17 (D3)
unnamed: OUTPUT_BUFFER_MEMORY1.7 (A6), U$3.15 (D2)
unnamed: OUTPUT_BUFFER_MEMORY1.8 (A7), U$3.14 (D1)
unnamed: OUTPUT_BUFFER_MEMORY1.9 (A8), U$3.13 (D0)
VCC: IC1.20 (VCC), IC2.20 (VCC), IC4.5 (VCC), OUTPUT_BUFFER_MEMORY.1 (DIR), OUTPUT_BUFFER_MEMORY.20 (VCC), OUTPUT_BUFFER_MEMORY1.1 (DIR), OUTPUT_BUFFER_MEMORY1.20 (VCC), U$1.VCC, U$1.VCC2 (VCC), U$2.31 (!WE), U$2.32 (VCC), U$3.32 (VCC)

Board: 2 copper layers, 8 parts (0 on the bottom side), 72 nets, no tracks yet.
